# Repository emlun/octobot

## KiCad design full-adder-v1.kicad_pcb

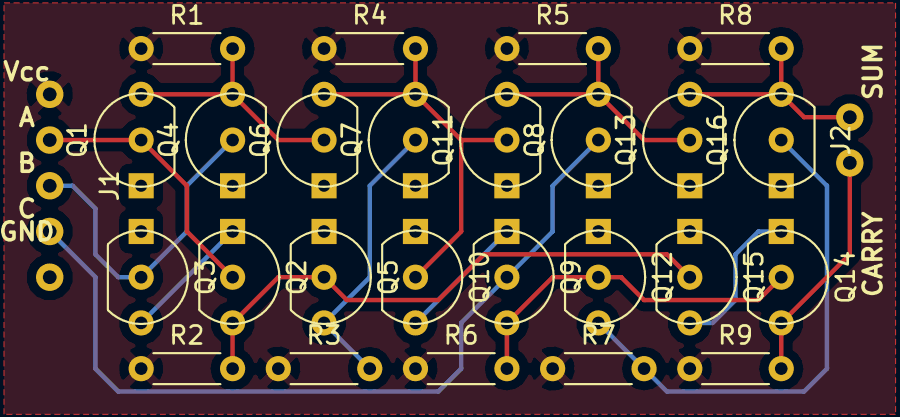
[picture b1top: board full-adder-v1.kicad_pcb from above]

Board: 2 copper layers, 27 parts (0 on the bottom side), 17 nets.

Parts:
J1: J5-5_pole_connector
J2: J2-2_pole_connector
Q1, Q2, Q3, Q4, Q5, Q6, Q7, Q8, Q9, Q10, Q11, Q12, Q13, Q14, Q15, Q16: 2N7000; TO-92_Molded_Wide_Inline
R1, R2, R3, R4, R5, R6, R7, R8, R9: 1M; R_Axial_DIN0204_L3.6mm_D1.6mm_P5.08mm_Horizontal

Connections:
/A: J1.2, Q1.2, Q2.2
/AandB: Q5.3, Q7.2, R3.2
/AnandB: Q2.3, Q5.2, Q15.2, R2.2
/AnorB: Q1.3, Q4.3, Q6.2, R1.2
/AnorBnorAandB: Q6.3, Q7.3, Q10.2, Q11.2, R4.2
/B: J1.3, Q3.2, Q4.2
/C: J1.4, Q8.2, Q9.2
/CandD: Q12.3, Q16.2, R7.2
/Carry: J2.2, Q14.3, R9.2
/CnandD: Q9.3, Q12.2, Q14.2, R6.2
/CnorD: Q8.3, Q11.3, Q13.2, R5.2
/CnorDnorCandD: J2.1, Q13.3, Q16.3, R8.2
/GND: J1.5, Q1.1, Q3.1, Q4.1, Q5.1, Q6.1, Q7.1, Q8.1, Q10.1, Q11.1, Q12.1, Q13.1, Q15.1, Q16.1
unnamed: Q2.1, Q3.3
unnamed: Q9.1, Q10.3
unnamed: Q14.1, Q15.3
VCC: J1.1, R1.1, R2.1, R3.1, R4.1, R5.1, R6.1, R7.1, R8.1, R9.1
